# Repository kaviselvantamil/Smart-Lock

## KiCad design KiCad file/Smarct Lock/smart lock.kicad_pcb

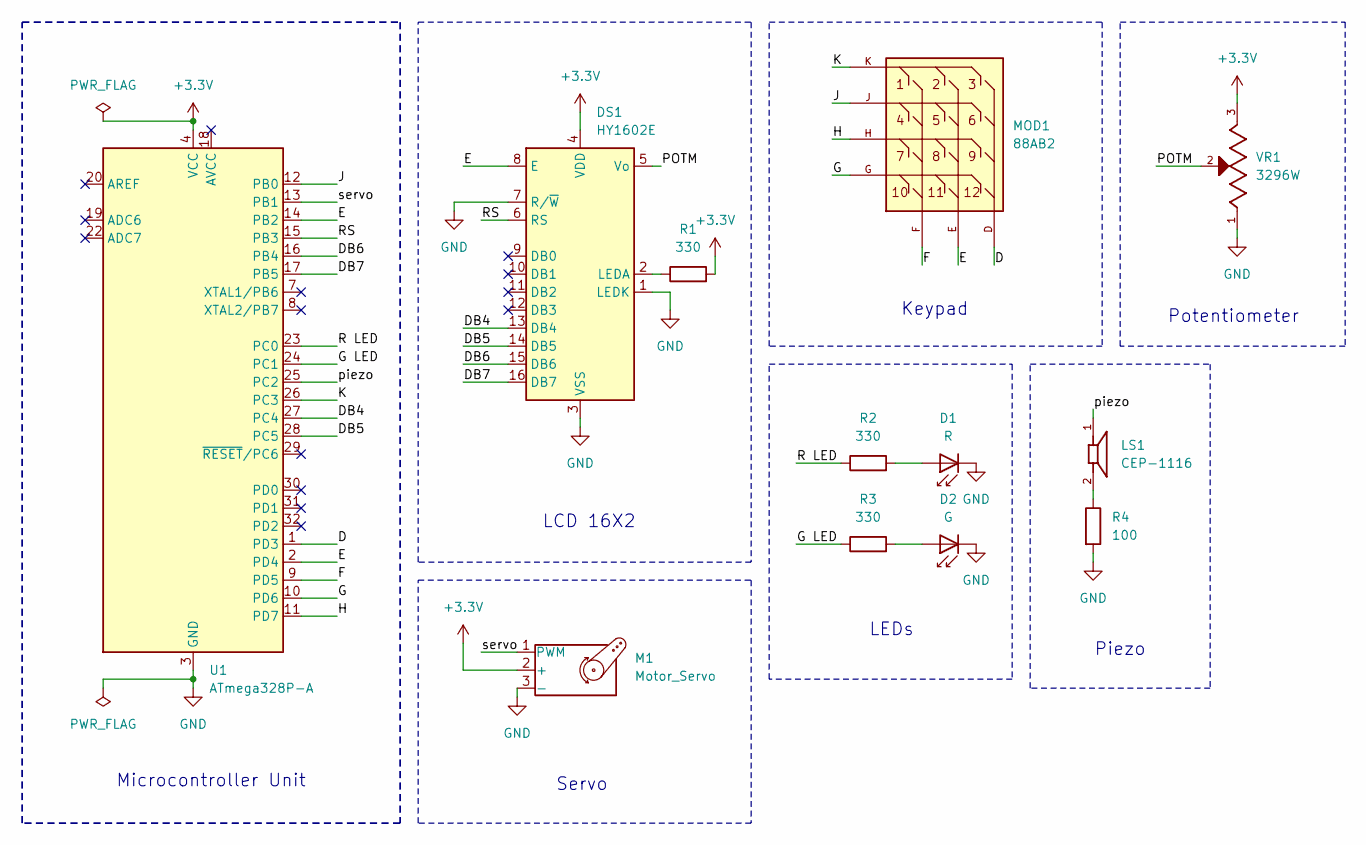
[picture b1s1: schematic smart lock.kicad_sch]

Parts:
D1: R; LED_D4.0mm
D2: G; LED_D4.0mm
DS1: HY1602E
LS1: CEP-1116; CUI_CEP-1116
M1: Motor_Servo; PinHeader_1x03_P2.54mm_Horizontal
MOD1: 88AB2
R1, R2, R3: 330; R_Axial_DIN0207_L6.3mm_D2.5mm_P15.24mm_Horizontal
R4: 100; R_Axial_DIN0207_L6.3mm_D2.5mm_P15.24mm_Horizontal
U1: ATmega328P-A; TQFP-32_7x7mm_P0.8mm
VR1: 3296W; Potentiometer_Bourns_3296W_Vertical; PARTREV 05/16

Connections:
+3.3V: DS1.4 (VDD), M1.2 (+), R1.2, U1.4 (VCC), U1.6 (VCC), VR1.3
/D: MOD1.D, U1.1 (PD3)
/DB4: DS1.13 (DB4), U1.27 (PC4)
/DB5: DS1.14 (DB5), U1.28 (PC5)
/DB6: DS1.15 (DB6), U1.16 (PB4)
/DB7: DS1.16 (DB7), U1.17 (PB5)
/E: DS1.8 (E), MOD1.E, U1.2 (PD4), U1.14 (PB2)
/F: MOD1.F, U1.9 (PD5)
/G: MOD1.G, U1.10 (PD6)
/G LED: R3.1, U1.24 (PC1)
/H: MOD1.H, U1.11 (PD7)
/J: MOD1.J, U1.12 (PB0)
/K: MOD1.K, U1.26 (PC3)
/POTM: DS1.5 (Vo), VR1.2
/R LED: R2.1, U1.23 (PC0)
/RS: DS1.6 (RS), U1.15 (PB3)
/piezo: LS1.1, U1.25 (PC2)
/servo: M1.1 (PWM), U1.13 (PB1)
GND: D1.1 (K), D2.1 (K), DS1.1 (LEDK), DS1.3 (VSS), DS1.7 (R/~W), M1.3 (-), R4.2, U1.3 (GND), U1.5 (GND), U1.21 (GND), VR1.1
unnamed: D1.2 (A), R2.2
unnamed: D2.2 (A), R3.2
unnamed: DS1.2 (LEDA), R1.1
unnamed: LS1.2, R4.1

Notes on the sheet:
Servo
LEDs
Piezo
LCD 16X2
Potentiometer
Microcontroller Unit
Keypad

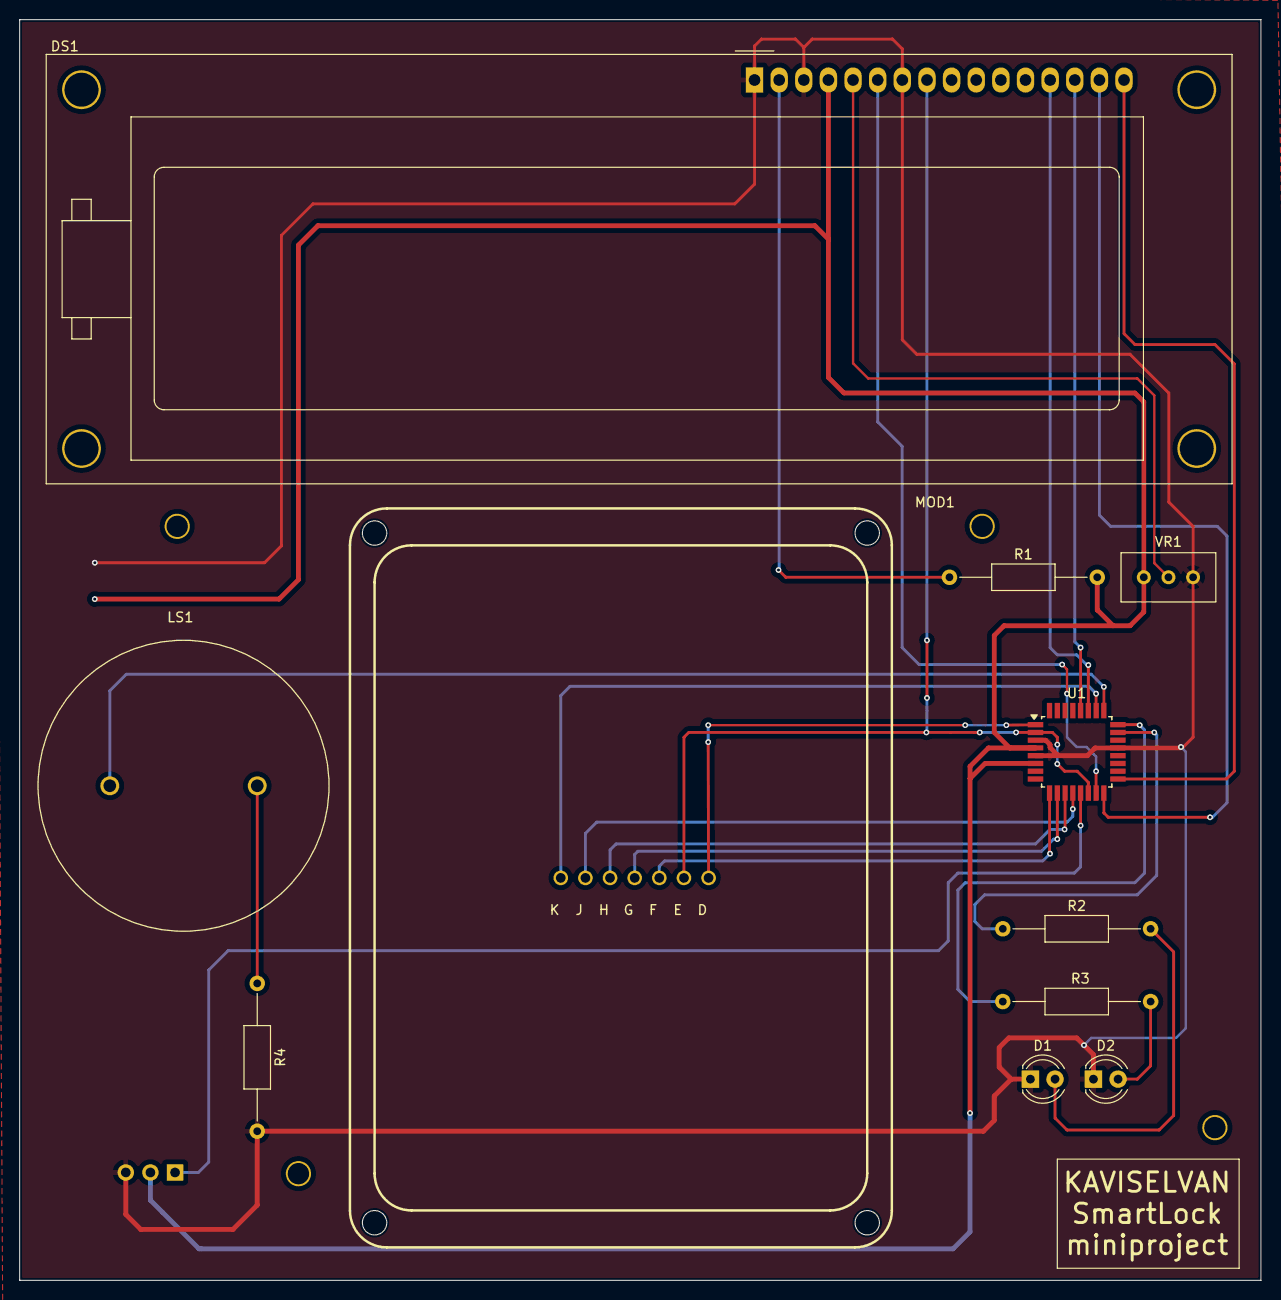
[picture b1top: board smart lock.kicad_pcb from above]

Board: 2 copper layers, 128.0 x 130.0 mm, 12 parts (1 on the bottom side), 23 nets.

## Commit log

2024-07-25 Create w
